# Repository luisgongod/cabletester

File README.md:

Eurorack Arduino 10/16 pin IDC Power Cable Tester
=================================================

Forked from [holmesrichards](https://github.com/holmesrichards/cabletester) Original idea and testing algorithm goes to [tomarus](https://github.com/tomarus/cabletester ). This version has a new PCB and Some modifications to the FW made into a Platformio project.

* It only tests (max) 8 wires because of how they're wired in eurorack.
* It can detect shorted cables or faulty/unconnected wires.
* Possible to run a _calibration_ sketch for more accurate readings.
* `GND-VCC-SCL-SDA` and `VCC-GND-SCL-SDA` Oled configuration allowed.
* JLCPCB Gerber ready zip

The original documentation and repo information is under _OGs_ folder. Gerbers, schematics and BOM are under _HW_ while the Platformio project is under _FW_.

# Calibration

Default values should work fine:
```
const int expect[] = {746, 544, 395, 286, 204, 130, 80, 35};
```
But is recommended to make a _calibration_ run to change to proper values. To do that:
- Define `DEBUG` mode by uncommenting line 7. 
- Plug a 16 pin Cable that is known to be work fine. 
- Flash the arduino and open Serialmonitor. the `expect` values will be printed, they should not differ too much from default values. 
- Change the `expect` values, comment the `DEBUG` define and re-flash

# Schematics

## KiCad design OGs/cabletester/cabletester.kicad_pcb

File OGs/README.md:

Arduino 10/16 pin Eurorack IDC Power Cable Tester
=================================================

Forked from [https://github.com/tomarus/cabletester](https://github.com/tomarus/cabletester) with slight modifications to circuit and software (mainly order of connections), and with PCB layout added.

* It only tests (max) 8 wires because of how they're wired in eurorack.
* It can detect shorted cables or faulty/unconnected wires.

This project uses a 128x64 OLED I2C display module with four interface pins: GND, +12V, SCL, and SDA. It is a monochrome display although it is available in a version with a yellow and blue overlay as seen in the photos. Note that the OLED pinout sometimes is GND-VCC-SCL-SDA and sometimes VCC-GND-SCL-SDA. The initial run of boards assumed the latter pinout; the present design has footprints for both.

These modules are available from the "usual suspects" on Amazon, eBay, AliExpress, etc. I have one of [these](https://www.amazon.com/gp/product/B072Q2X2LL) (GND-VCC-SCL-SDA) and one of [these](https://www.amazon.com/gp/product/B07FK8GB8T) (VCC-GND-SCL-SDA). They do *not* seem to be available from any established vendors like Mouser, DigiKey, Tayda, Adafruit, or SparkFun. Please make sure you have a source for the display before proceeding with this project! 

Code uses these libraries:

* https://github.com/adafruit/Adafruit_SSD1306
* https://github.com/adafruit/Adafruit-GFX-Library

# Schematics

# PCB

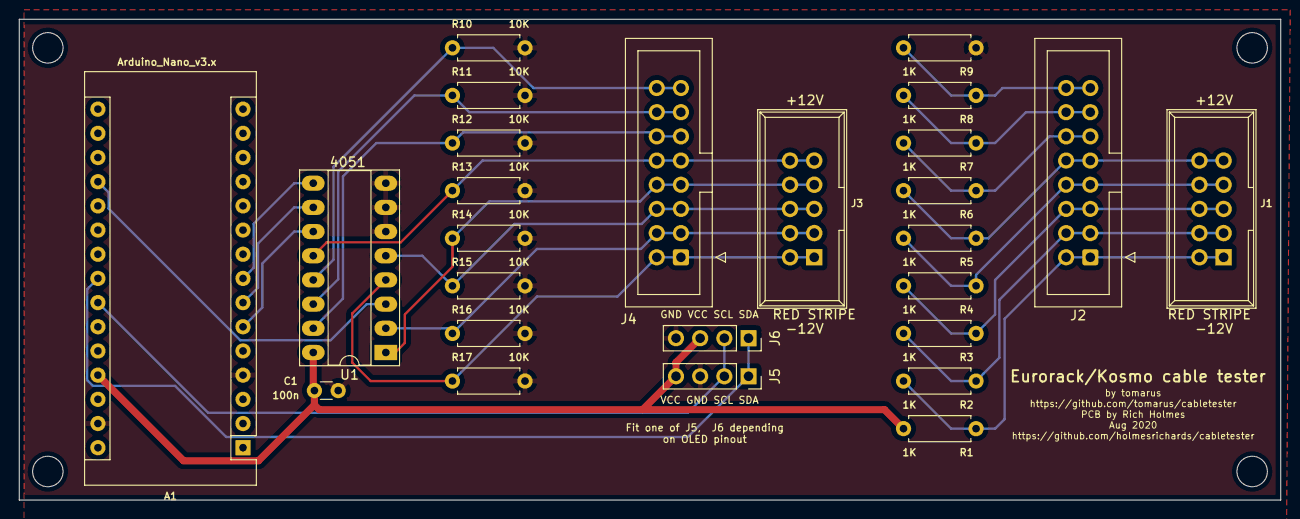
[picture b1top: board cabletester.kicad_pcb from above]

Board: 2 copper layers, 132.5 x 50.5 mm, 26 parts (0 on the bottom side), 24 nets.

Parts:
A1: Arduino_Nano_v3.x; Arduino_Nano
C1: 100n; C_Disc_D3.0mm_W1.6mm_P2.50mm
J1, J3: IDC 2x5; Power_Header
J2, J4: IDC 2x8; IDC-Header_2x08_P2.54mm_Vertical
J5, J6: 4 pin header; PinSocket_1x04_P2.54mm_Vertical
R1, R2, R3, R4, R5, R6, R7, R8, R9: 1K; R_Axial_DIN0207_L6.3mm_D2.5mm_P7.62mm_Horizontal
R10, R11, R12, R13, R14, R15, R16, R17: 10K; R_Axial_DIN0207_L6.3mm_D2.5mm_P7.62mm_Horizontal
U1: 4051; DIP-16_W7.62mm_Socket_LongPads

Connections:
+5V: A1.27, C1.1, J5.4, J6.3, R1.2, U1.16
A4: A1.23, J5.1, J6.1
A5: A1.24, J5.2, J6.2
GND: A1.4, A1.29, C1.2, J5.3, J6.4, R9.1, R10.2, R11.2, R12.2, R13.2, R14.2, R15.2, R16.2, R17.2, U1.6, U1.7, U1.8
unnamed: A1.19, U1.3
unnamed: J1.1, J1.2, J2.1, J2.2, R1.1, R2.2
unnamed: J1.3, J1.4, J2.3, J2.4, R2.1, R3.2
unnamed: J1.5, J1.6, J2.5, J2.6, R3.1, R4.2
unnamed: J1.7, J1.8, J2.7, J2.8, R4.1, R5.2
unnamed: J1.9, J1.10, J2.9, J2.10, R5.1, R6.2
unnamed: J2.11, J2.12, R6.1, R7.2
unnamed: J2.13, J2.14, R7.1, R8.2
unnamed: J2.15, J2.16, R8.1, R9.2
unnamed: J3.1, J3.2, J4.1, J4.2, R17.1, U1.4
unnamed: J3.3, J3.4, J4.3, J4.4, R16.1, U1.2
unnamed: J3.5, J3.6, J4.5, J4.6, R15.1, U1.5
unnamed: J3.7, J3.8, J4.7, J4.8, R14.1, U1.1
unnamed: J3.9, J3.10, J4.9, J4.10, R13.1, U1.12
unnamed: J4.11, J4.12, R12.1, U1.15
unnamed: J4.13, J4.14, R11.1, U1.14
unnamed: J4.15, J4.16, R10.1, U1.13
S0: A1.6, U1.11
S1: A1.7, U1.10
S2: A1.8, U1.9

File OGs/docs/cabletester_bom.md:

# cabletester BOM

Tue 11 Aug 2020 08:37:09 AM EDT

Generated from schematic by Eeschema 5.1.6-c6e7f7d~86~ubuntu18.04.1

**Component Count:** 26

| Value | Qty | Part | Description | Vendor |
| ----- | --- | ---- | ----------- | ------ |
| A1 | 1 | Arduino_Nano_v3.x | Arduino Nano v3.x | Tayda A-2864 |
| C1 | 1 | 100 nF | Unpolarized capacitor | Tayda A-564 |
| J1, J3 | 2 | IDC 2x5 | Eurorack style 10 pin power header | Tayda A-2939 |
| J2, J4 | 2 | IDC 2x8 | Eurorack style 16 pin power header | Tayda A-2956 |
| J5, J6 | 1 | 4 pin header | 4 pin female 2.54 mm header (fit in one of two locations) | Tayda A-1303 |
| R1, R2, R3, R4, R5, R6, R7, R8, R9 | 9 | 1K | Resistor | Tayda A-2200 |
| R10, R11, R12, R13, R14, R15, R16, R17 | 8 | 10K | Resistor | Tayda A-2203 |
| U1 | 1 | 4051 | Analog Multiplexer 8 to 1 | Tayda A-026 |
| – | 1 | – | 128x64 monochrome I2C OLED module | eBay, AliExpress... |

See [README](../README.md) for notes on OLED module.

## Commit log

2022-07-17 ✨ working pcb
2022-07-24 🔖 Release
2022-07-24 📝 zip reference
